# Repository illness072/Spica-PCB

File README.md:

# Spica PCB

PCB Data for Spica Keyboard

Spica is a 38-keys keyboard inspired by the Gemini Keyboard layout by zk-phi(@zk-phi). It was named by Sumiso(@kutsuhimo3).

* Gemini Keyboard by @zk-phi
  * https://github.com/zk-phi/gemini-keyboard

* Case Data
  * https://github.com/illness072/Spica-case/

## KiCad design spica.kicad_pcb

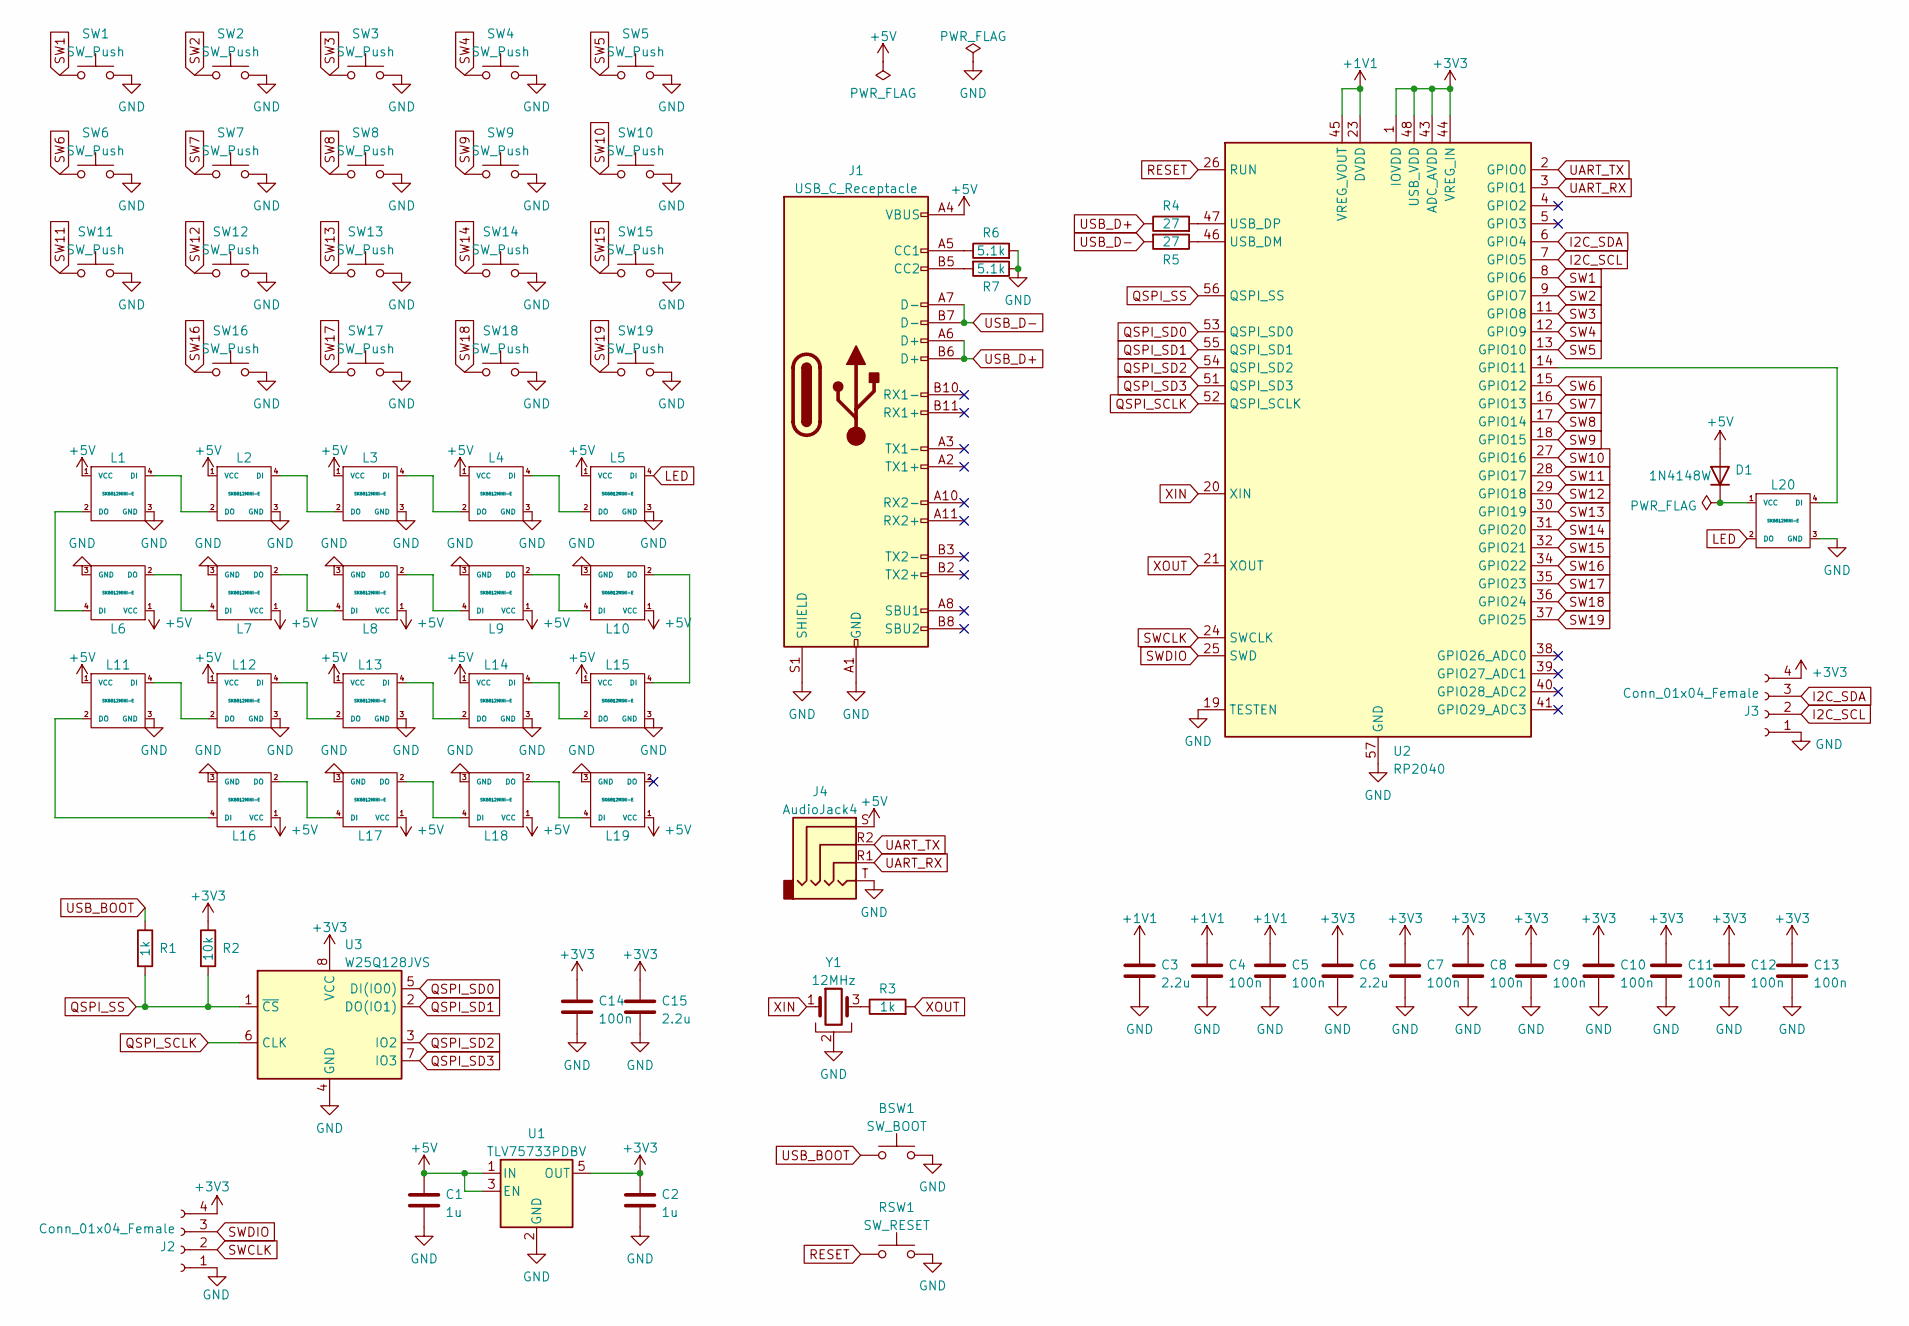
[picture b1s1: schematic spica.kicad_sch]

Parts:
BSW1: SW_BOOT; SW_Push_1P1T_NO_Vertical_Wuerth_434133025816
C1, C2: 1u; C_0402_1005Metric; LCSC C52923
C3, C6, C15: 2.2u; C_0402_1005Metric; LCSC C307418
C4, C5, C7, C8, C9, C10, C11, C12, C13: 100n; C_0402_1005Metric; LCSC C1525
C14: 100n; C_0402_1005Metric
D1: 1N4148W; D_SOD-123; LCSC C109203
J1: USB_C_Receptacle; USB_C_Receptacle_HRO_TYPE-C-31-M-12; LCSC C165948
J2, J3: Conn_01x04_Female; PinSocket_1x04_P2.54mm_Vertical
J4: AudioJack4; MJ-4PP-9_cross
L1, L2, L3, L4, L5, L6, L7, L8, L9, L10, L11, L12, L13, L14, L15, L16, L17, L18, L19, L20: SK6812MINI-E; SK6812MINI-E_Rev
R1, R3: 1k; R_0402_1005Metric; LCSC C11702
R2: 10k; R_0402_1005Metric; LCSC C25744
R4, R5: 27; R_0402_1005Metric; LCSC C25100
R6, R7: 5.1k; R_0402_1005Metric; LCSC C25905
RSW1: SW_RESET; SW_Push_1P1T_NO_Vertical_Wuerth_434133025816
SW1, SW2, SW3, SW4, SW5, SW7, SW8, SW9, SW10, SW12, SW13, SW14, SW15, SW16, SW17, SW18, SW19: SW_Push; MX_1.00u-reversible
SW6: SW_Push; MX_1.25u-reversible
SW11: SW_Push; MX_1.50u-reversible
U1: TLV75733PDBV; SOT-23-5; LCSC C485517
U2: RP2040; QFN-56-1EP_7x7mm_P0.4mm_EP3.2x3.2mm; LCSC C2040
U3: W25Q128JVS; WSON-8-1EP_6x5mm_P1.27mm_EP3.4x4.3mm; LCSC C190862
Y1: 12MHz; Resonator_SMD_Murata_CSTxExxV-3Pin_3.0x1.1mm; LCSC C341520

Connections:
+1V1: C3.1, C4.1, C5.1, U2.23 (DVDD), U2.45 (VREG_VOUT), U2.50 (DVDD)
+3V3: C2.1, C6.1, C7.1, C8.1, C9.1, C10.1, C11.1, C12.1, C13.1, C14.1, C15.1, J2.4, J3.4, R2.1, U1.5 (OUT), U2.1 (IOVDD), U2.10 (IOVDD), U2.22 (IOVDD), U2.33 (IOVDD), U2.42 (IOVDD), U2.43 (ADC_AVDD), U2.44 (VREG_IN), U2.48 (USB_VDD), U2.49 (IOVDD), U3.8 (VCC)
+5V: C1.1, D1.2 (A), J1.A4 (VBUS), J1.A9 (VBUS), J1.B4 (VBUS), J1.B9 (VBUS), J4.S, L1.1 (VCC), L2.1 (VCC), L3.1 (VCC), L4.1 (VCC), L5.1 (VCC), L6.1 (VCC), L7.1 (VCC), L8.1 (VCC), L9.1 (VCC), L10.1 (VCC), L11.1 (VCC), L12.1 (VCC), L13.1 (VCC), L14.1 (VCC), L15.1 (VCC), L16.1 (VCC), L17.1 (VCC), L18.1 (VCC), L19.1 (VCC), U1.1 (IN), U1.3 (EN)
GND: BSW1.2, C1.2, C2.2, C3.2, C4.2, C5.2, C6.2, C7.2, C8.2, C9.2, C10.2, C11.2, C12.2, C13.2, C14.2, C15.2, J1.A1 (GND), J1.A12 (GND), J1.B1 (GND), J1.B12 (GND), J1.S1 (SHIELD), J2.1, J3.1, J4.T, L1.3 (GND), L2.3 (GND), L3.3 (GND), L4.3 (GND), L5.3 (GND), L6.3 (GND), L7.3 (GND), L8.3 (GND), L9.3 (GND), L10.3 (GND), L11.3 (GND), L12.3 (GND), L13.3 (GND), L14.3 (GND), L15.3 (GND), L16.3 (GND), L17.3 (GND), L18.3 (GND), L19.3 (GND), L20.3 (GND), R6.2, R7.1, RSW1.2, SW1.2, SW2.2, SW3.2, SW4.2, SW5.2, SW6.2, SW7.2, SW8.2, SW9.2, SW10.2, SW11.2, SW12.2, SW13.2, SW14.2, SW15.2, SW16.2, SW17.2, SW18.2, SW19.2, U1.2 (GND), U2.19 (TESTEN), U2.57 (GND), U3.4 (GND), Y1.2
I2C_SCL: J3.2, U2.7 (GPIO5)
I2C_SDA: J3.3, U2.6 (GPIO4)
LED: L5.4 (DI), L20.2 (DO)
unnamed: D1.1 (K), L20.1 (VCC)
unnamed: J1.A5 (CC1), R6.1
unnamed: J1.B5 (CC2), R7.2
unnamed: L1.2 (DO), L6.4 (DI)
unnamed: L1.4 (DI), L2.2 (DO)
unnamed: L2.4 (DI), L3.2 (DO)
unnamed: L3.4 (DI), L4.2 (DO)
unnamed: L4.4 (DI), L5.2 (DO)
unnamed: L6.2 (DO), L7.4 (DI)
unnamed: L7.2 (DO), L8.4 (DI)
unnamed: L8.2 (DO), L9.4 (DI)
unnamed: L10.2 (DO), L15.4 (DI)
unnamed: L9.2 (DO), L10.4 (DI)
unnamed: L11.2 (DO), L16.4 (DI)
unnamed: L11.4 (DI), L12.2 (DO)
unnamed: L12.4 (DI), L13.2 (DO)
unnamed: L13.4 (DI), L14.2 (DO)
unnamed: L14.4 (DI), L15.2 (DO)
unnamed: L16.2 (DO), L17.4 (DI)
unnamed: L17.2 (DO), L18.4 (DI)
unnamed: L18.2 (DO), L19.4 (DI)
unnamed: L20.4 (DI), U2.14 (GPIO11)
unnamed: R3.1, Y1.3
unnamed: R4.2, U2.47 (USB_DP)
unnamed: R5.1, U2.46 (USB_DM)
QSPI_SCLK: U2.52 (QSPI_SCLK), U3.6 (CLK)
QSPI_SD0: U2.53 (QSPI_SD0), U3.5 (DI(IO0))
QSPI_SD1: U2.55 (QSPI_SD1), U3.2 (DO(IO1))
QSPI_SD2: U2.54 (QSPI_SD2), U3.3 (IO2)
QSPI_SD3: U2.51 (QSPI_SD3), U3.7 (IO3)
QSPI_SS: R1.2, R2.2, U2.56 (QSPI_SS), U3.1 (~CS)
RESET: RSW1.1, U2.26 (RUN)
SW1: SW1.1, U2.8 (GPIO6)
SW2: SW2.1, U2.9 (GPIO7)
SW3: SW3.1, U2.11 (GPIO8)
SW4: SW4.1, U2.12 (GPIO9)
SW5: SW5.1, U2.13 (GPIO10)
SW6: SW6.1, U2.15 (GPIO12)
SW7: SW7.1, U2.16 (GPIO13)
SW8: SW8.1, U2.17 (GPIO14)
SW9: SW9.1, U2.18 (GPIO15)
SW10: SW10.1, U2.27 (GPIO16)
SW11: SW11.1, U2.28 (GPIO17)
SW12: SW12.1, U2.29 (GPIO18)
SW13: SW13.1, U2.30 (GPIO19)
SW14: SW14.1, U2.31 (GPIO20)
SW15: SW15.1, U2.32 (GPIO21)
SW16: SW16.1, U2.34 (GPIO22)
SW17: SW17.1, U2.35 (GPIO23)
SW18: SW18.1, U2.36 (GPIO24)
SW19: SW19.1, U2.37 (GPIO25)
SWCLK: J2.2, U2.24 (SWCLK)
SWDIO: J2.3, U2.25 (SWD)
UART_RX: J4.R1, U2.3 (GPIO1)
UART_TX: J4.R2, U2.2 (GPIO0)
USB_BOOT: BSW1.1, R1.1
USB_D+: J1.A6 (D+), J1.B6 (D+), R4.1
USB_D-: J1.A7 (D-), J1.B7 (D-), R5.2
XIN: U2.20 (XIN), Y1.1
XOUT: R3.2, U2.21 (XOUT)

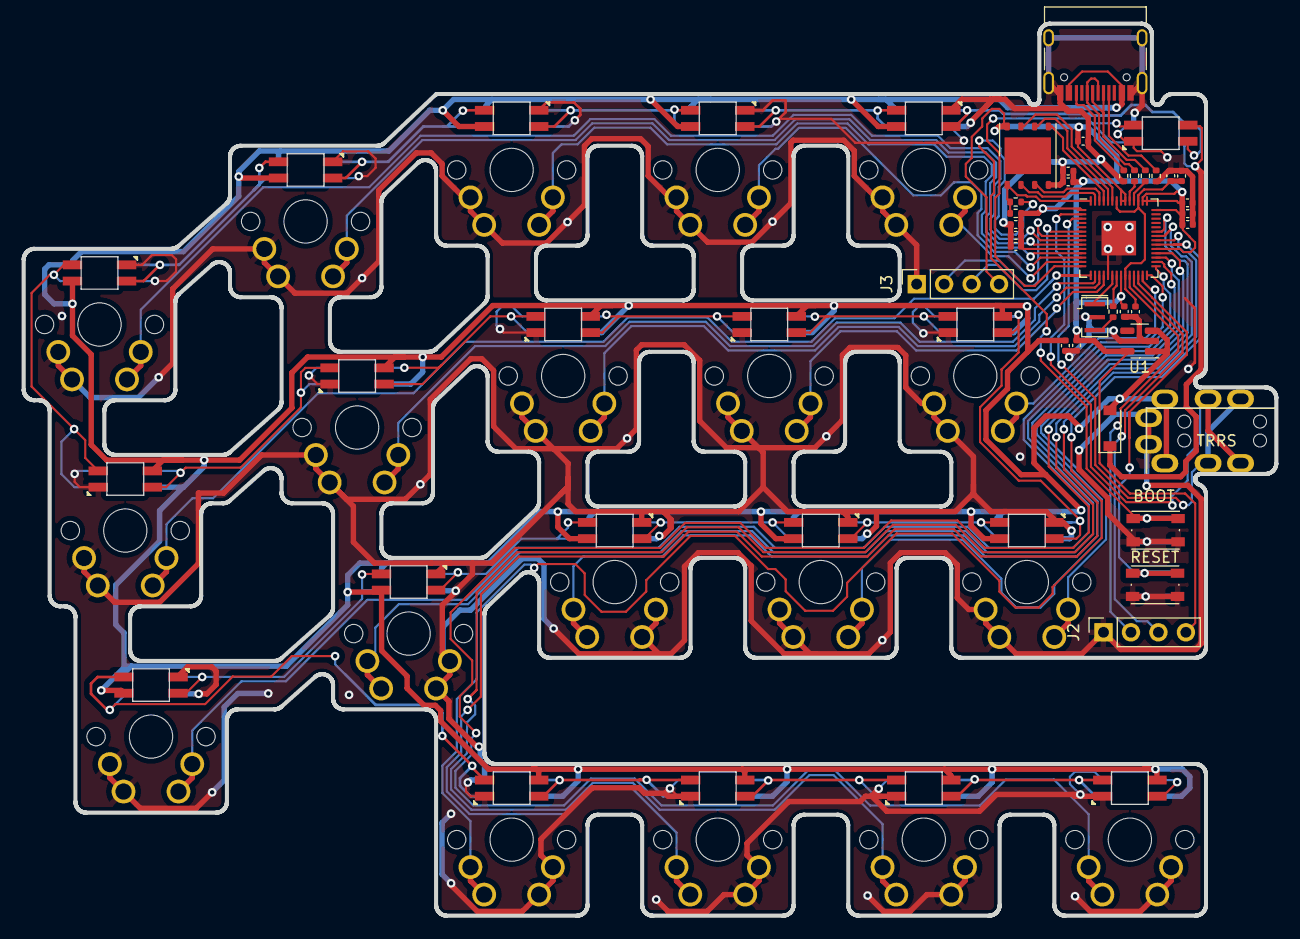
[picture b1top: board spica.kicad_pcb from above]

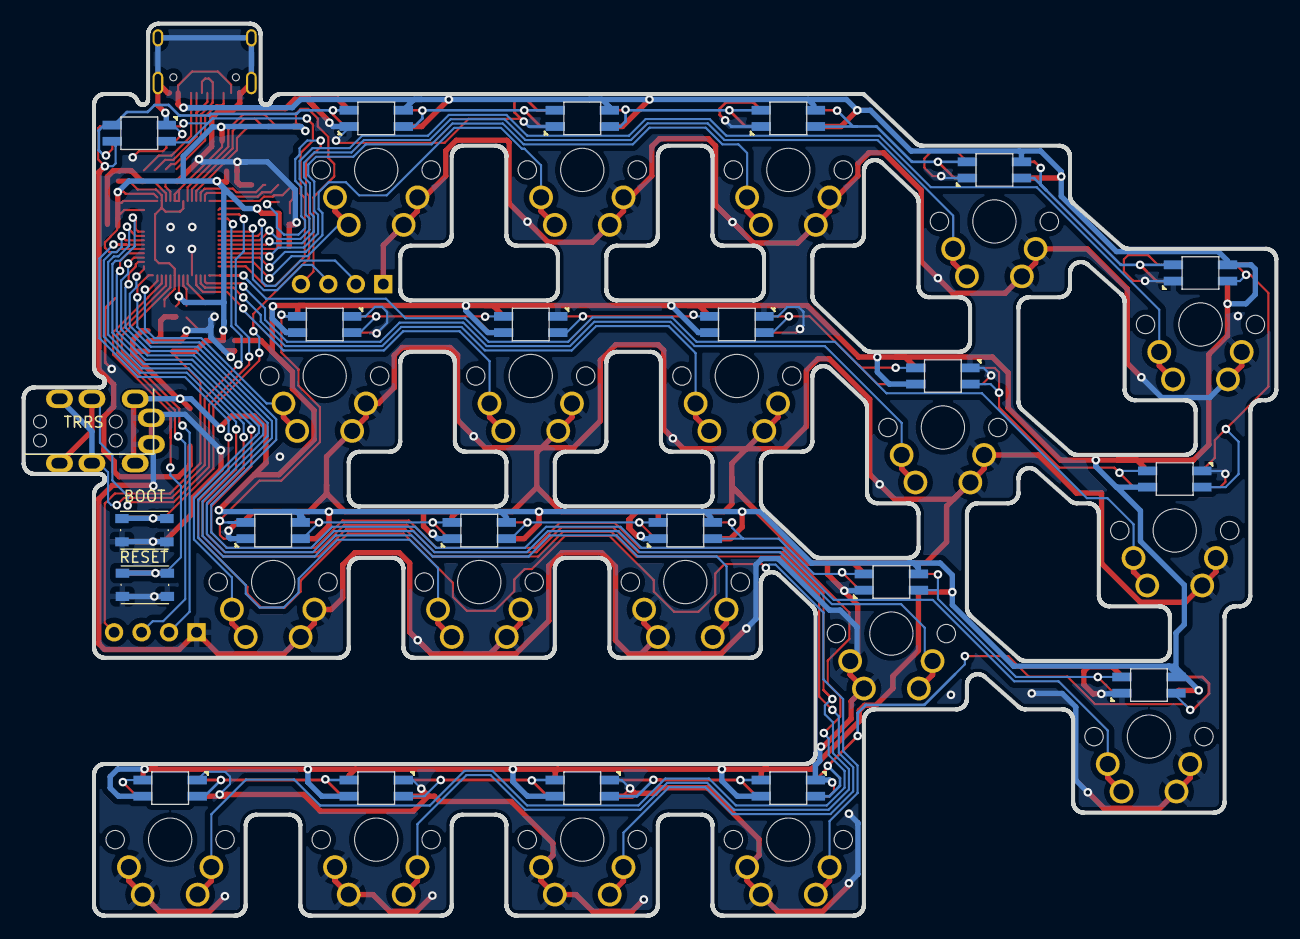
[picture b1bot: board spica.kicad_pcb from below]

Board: 2 copper layers, 115.8 x 82.5 mm, 72 parts (6 on the bottom side), 67 nets.

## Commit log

2023-12-20 first version
